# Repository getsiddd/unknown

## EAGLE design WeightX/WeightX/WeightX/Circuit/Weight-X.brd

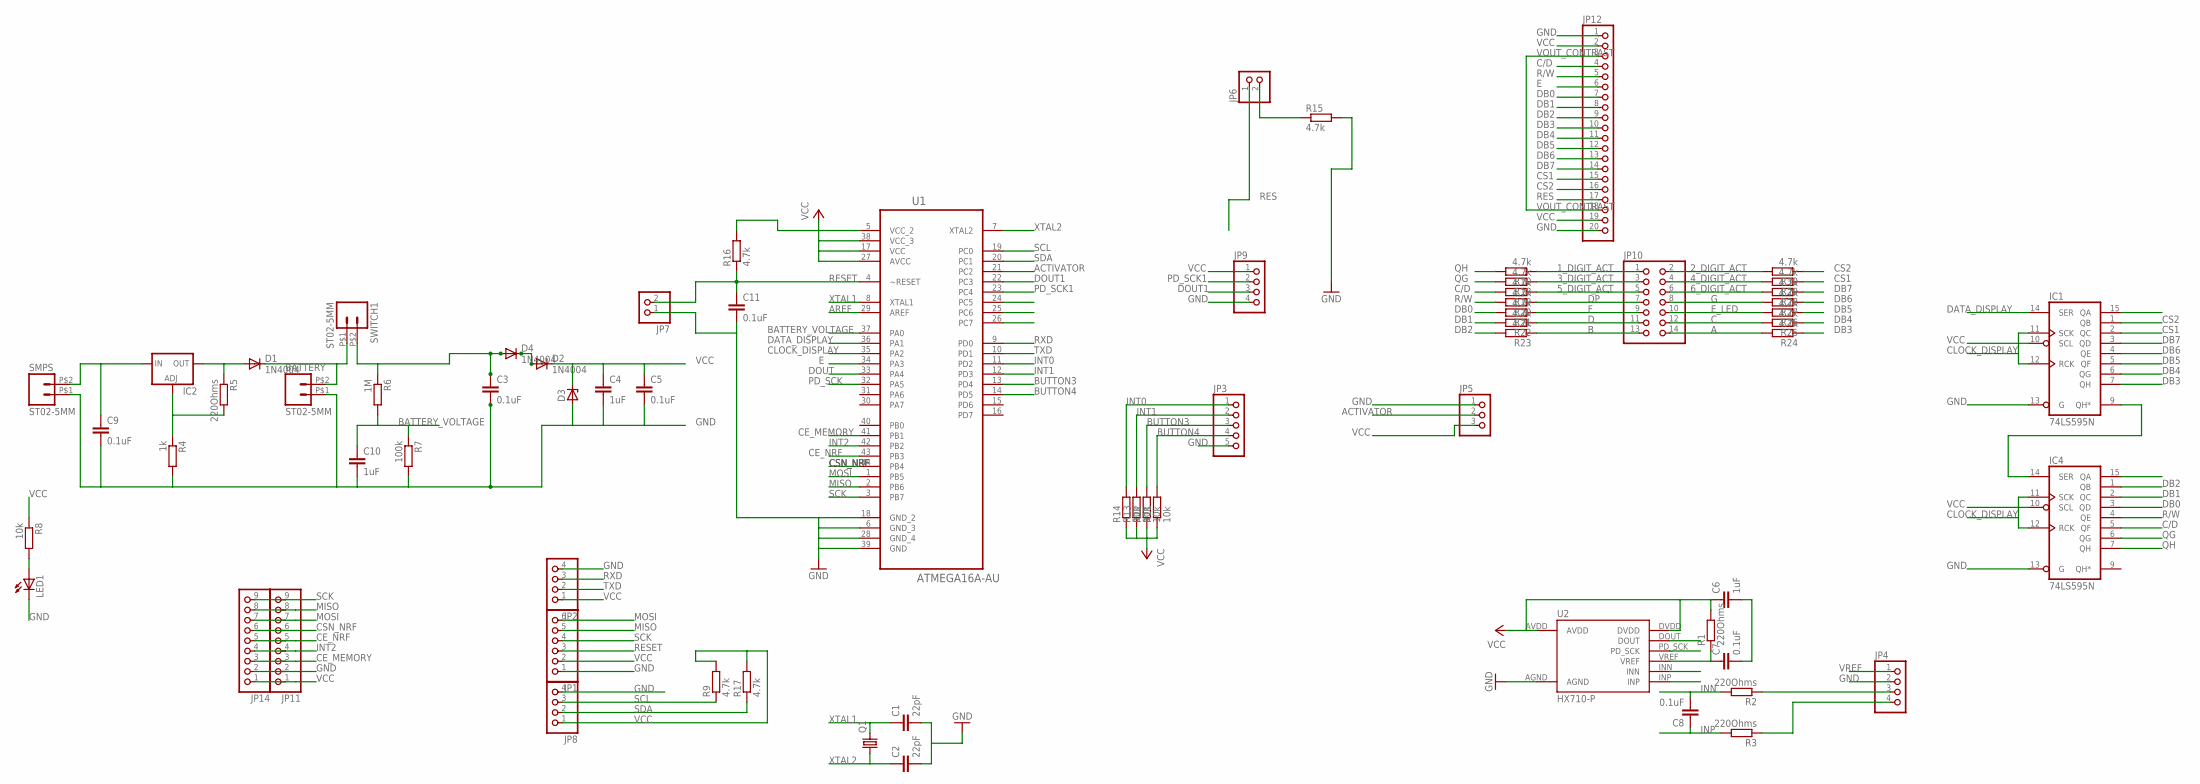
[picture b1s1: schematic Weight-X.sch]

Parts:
BATTERY: ST02-5MM; EK500V-02P
C1, C2: 22pF; C2.5-2
C3, C5, C7, C8, C9, C11: 0.1uF; C5B2.5
C4, C6, C10: 1uF; C5B2.5
D1, D2, D4: 1N4004; DO41-10
D3: ZENER-DIODEC1702-15; C1702-15
IC1, IC4: 74LS595N; DIL16
IC2: LM317TS; 317TS
JP1: PINHD-1X6; 1X06
JP2, JP4, JP8, JP9: PINHD-1X4; 1X04
JP3: PINHD-1X5; 1X05
JP5: PINHD-1X3; 1X03
JP6, JP7: PINHD-1X2; 1X02
JP10: PINHD-2X7; 2X07
JP11, JP14: PINHD-1X9; 1X09
JP12: PINHD-1X20; 1X20
LED1: LED5MM
Q1: CRYSTALHC49U-V; HC49U-V
R1, R2, R3, R5: 220Ohms; 0204/7
R4: 1k; 0204/7
R6: 1M; 0204/7
R7: 100k; 0204/7
R8, R11, R12, R13, R14: 10k; 0204/7
R9, R10, R15, R16, R17, R18, R19, R20, R21, R22, R23, R24, R25, R26, R27, R28, R29, R30: 4.7k; 0204/7
SMPS: ST02-5MM; EK500V-02P
SWITCH1: ST02-5MM; EK500V-02P
U1: ATMEGA16A-AU; QFP80P1200X1200X120-44N
U2: HX710-P; PDIP08_300MIL

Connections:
1_DIGIT_ACT: JP10.1, R10.1
2_DIGIT_ACT: JP10.2, R30.2
3_DIGIT_ACT: JP10.3, R18.1
4_DIGIT_ACT: JP10.4, R29.2
5_DIGIT_ACT: JP10.5, R19.1
6_DIGIT_ACT: JP10.6, R28.2
A: JP10.14, R24.2
ACTIVATOR: JP5.2, U1.21 (PC2)
AREF: U1.29 (AREF)
B: JP10.13, R23.1
BATTERY_VOLTAGE: C10.1, R6.2, R7.1, U1.37 (PA0)
BUTTON3: JP3.3, R12.2, U1.13 (PD4)
BUTTON4: JP3.4, R11.2, U1.14 (PD5)
C: JP10.12, R25.2
C/D: IC4.5 (QF), JP12.4, R19.2
CE_MEMORY: JP11.3, JP14.3, U1.41 (PB1)
CE_NRF: JP11.5, JP14.5, U1.43 (PB3)
CLOCK_DISPLAY: IC1.11 (SCK), IC1.12 (RCK), IC4.11 (SCK), IC4.12 (RCK), U1.35 (PA2)
CS1: IC1.2 (QC), JP12.15, R29.1
CS2: IC1.1 (QB), JP12.16, R30.1
CSN_NRF: JP11.6, JP14.6, U1.44 (PB4)
D: JP10.11, R22.1
DATA_DISPLAY: IC1.14 (SER), U1.36 (PA1)
DB0: IC4.3 (QD), JP12.7, R21.2
DB1: IC4.2 (QC), JP12.8, R22.2
DB2: IC4.1 (QB), JP12.9, R23.2
DB3: IC1.7 (QH), JP12.10, R24.1
DB4: IC1.6 (QG), JP12.11, R25.1
DB5: IC1.5 (QF), JP12.12, R26.1
DB6: IC1.4 (QE), JP12.13, R27.1
DB7: IC1.3 (QD), JP12.14, R28.1
DOUT: U1.33 (PA4), U2.DOUT
DOUT1: JP9.3, U1.22 (PC3)
DP: JP10.7, R20.1
E: JP12.6, U1.34 (PA3)
E_LED: JP10.10, R26.2
F: JP10.9, R21.1
G: JP10.8, R27.2
GND: BATTERY.P$1 (1), C1.2, C2.2, C3.2, C4.2, C5.2, C6.2, C7.2, C9.2, C10.2, C11.2, D3.A, IC1.8 (GND), IC1.13 (G), IC4.8 (GND), IC4.13 (G), JP1.1, JP2.4, JP3.5, JP4.2, JP5.1, JP7.1, JP8.4, JP9.4, JP11.2, JP12.1, JP12.20, JP14.2, LED1.K (C), R4.2, R7.2, R15.2, SMPS.P$1 (1), U1.6 (GND_3), U1.18 (GND_2), U1.28 (GND_4), U1.39 (GND), U2.AGND
INN: C8.2, R2.2, U2.INN
INP: C8.1, R3.2, U2.INP
INT0: JP3.1, R14.2, U1.11 (PD2)
INT1: JP3.2, R13.2, U1.12 (PD3)
INT2: JP11.4, JP14.4, U1.42 (PB2)
MISO: JP1.5, JP11.8, JP14.8, U1.2 (PB6)
MOSI: JP1.6, JP11.7, JP14.7, U1.1 (PB5)
unnamed: BATTERY.P$2 (2), D1.C, SWITCH1.P$1 (1)
unnamed: IC2.1 (ADJ), R4.1, R5.2
unnamed: LED1.A, R8.2
unnamed: D1.A, IC2.2 (OUT), R5.1
unnamed: JP4.3, R2.1
unnamed: D2.A, D4.C
unnamed: C9.1, IC2.3 (IN), SMPS.P$2 (2)
unnamed: C3.1, D4.A, R6.1, SWITCH1.P$2 (2)
unnamed: JP4.4, R3.1
unnamed: JP6.2, R15.1
unnamed: IC1.9 (QH*), IC4.14 (SER)
PD_SCK: U1.32 (PA5), U2.PD_SCK
PD_SCK1: JP9.2, U1.23 (PC4)
QG: IC4.6 (QG), R18.2
QH: IC4.7 (QH), R10.2
R/W: IC4.4 (QE), JP12.5, R20.2
RES: JP6.1, JP12.17
RESET: C11.1, JP1.3, JP7.2, R16.1, U1.4 (~RESET)
RXD: JP2.3, U1.9 (PD0)
SCK: JP1.4, JP11.9, JP14.9, U1.3 (PB7)
SCL: JP8.3, R9.1, U1.19 (PC0)
SDA: JP8.2, R17.1, U1.20 (PC1)
TXD: JP2.2, U1.10 (PD1)
VCC: C4.1, C5.1, C6.1, D2.C, D3.C, IC1.10 (SCL), IC1.16 (VCC), IC4.10 (SCL), IC4.16 (VCC), JP1.2, JP2.1, JP5.3, JP8.1, JP9.1, JP11.1, JP12.2, JP12.19, JP14.1, R1.2, R8.1, R9.2, R11.1, R12.1, R13.1, R14.1, R16.2, R17.2, U1.5 (VCC_2), U1.17 (VCC), U1.27 (AVCC), U1.38 (VCC_3), U2.AVDD, U2.DVDD
VOUT_CONTRAST: JP12.3, JP12.18
VREF: C7.1, JP4.1, R1.1, U2.VREF
XTAL1: C1.1, Q1.2, U1.8 (XTAL1)
XTAL2: C2.1, Q1.1, U1.7 (XTAL2)

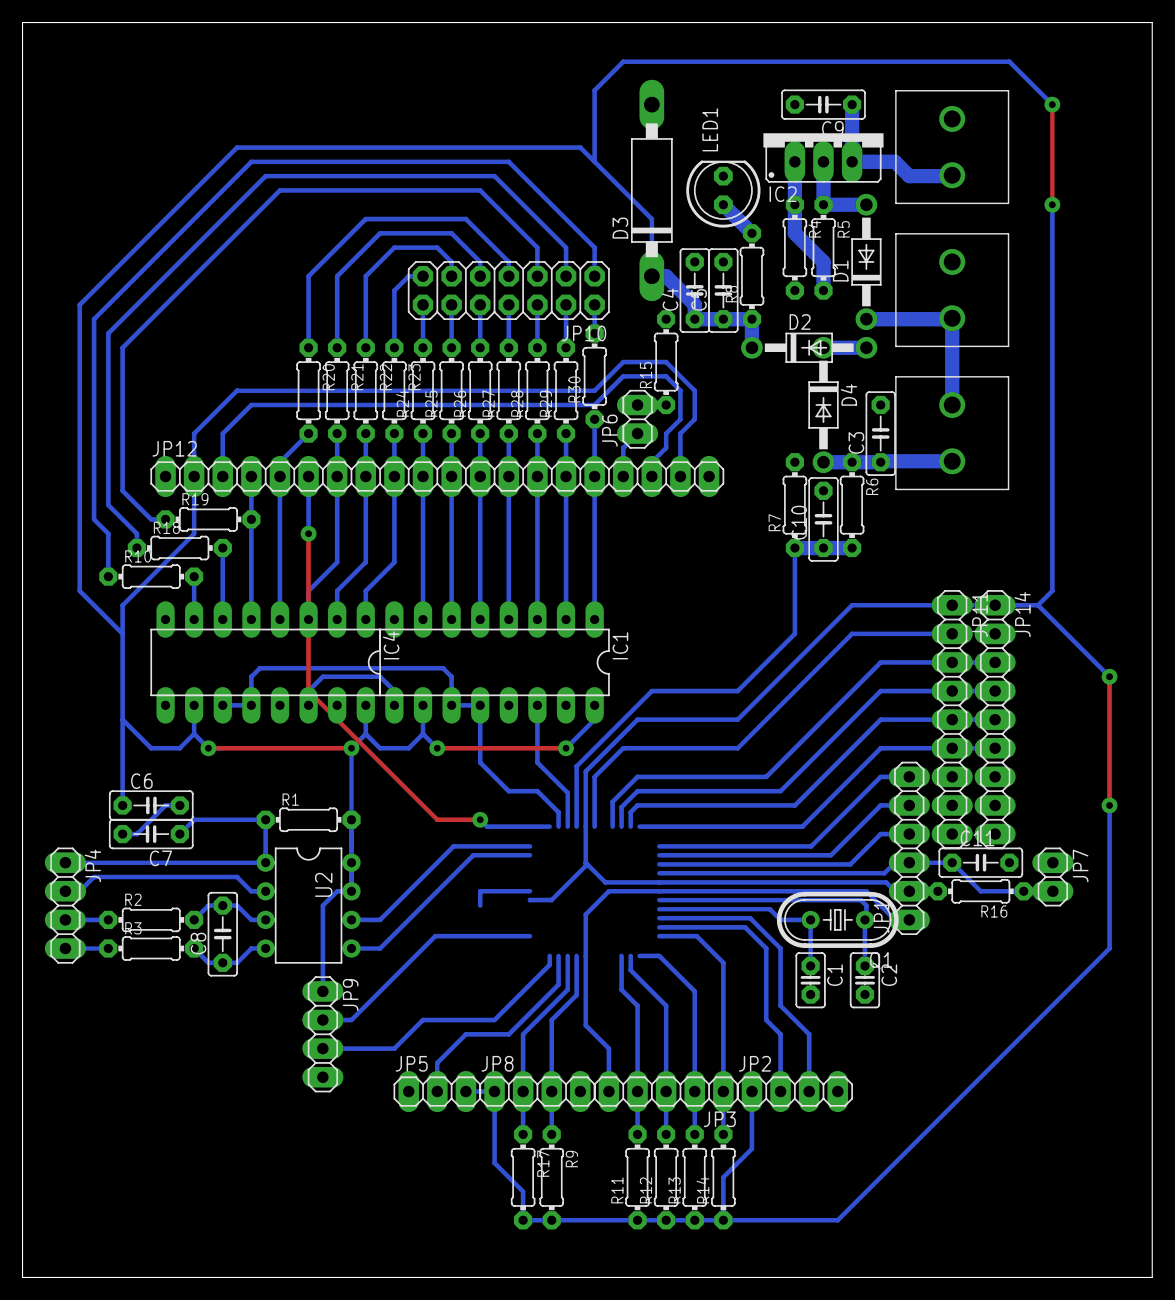
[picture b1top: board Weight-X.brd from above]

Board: 2 copper layers, 100.3 x 111.4 mm, 68 parts (1 on the bottom side), 73 nets.

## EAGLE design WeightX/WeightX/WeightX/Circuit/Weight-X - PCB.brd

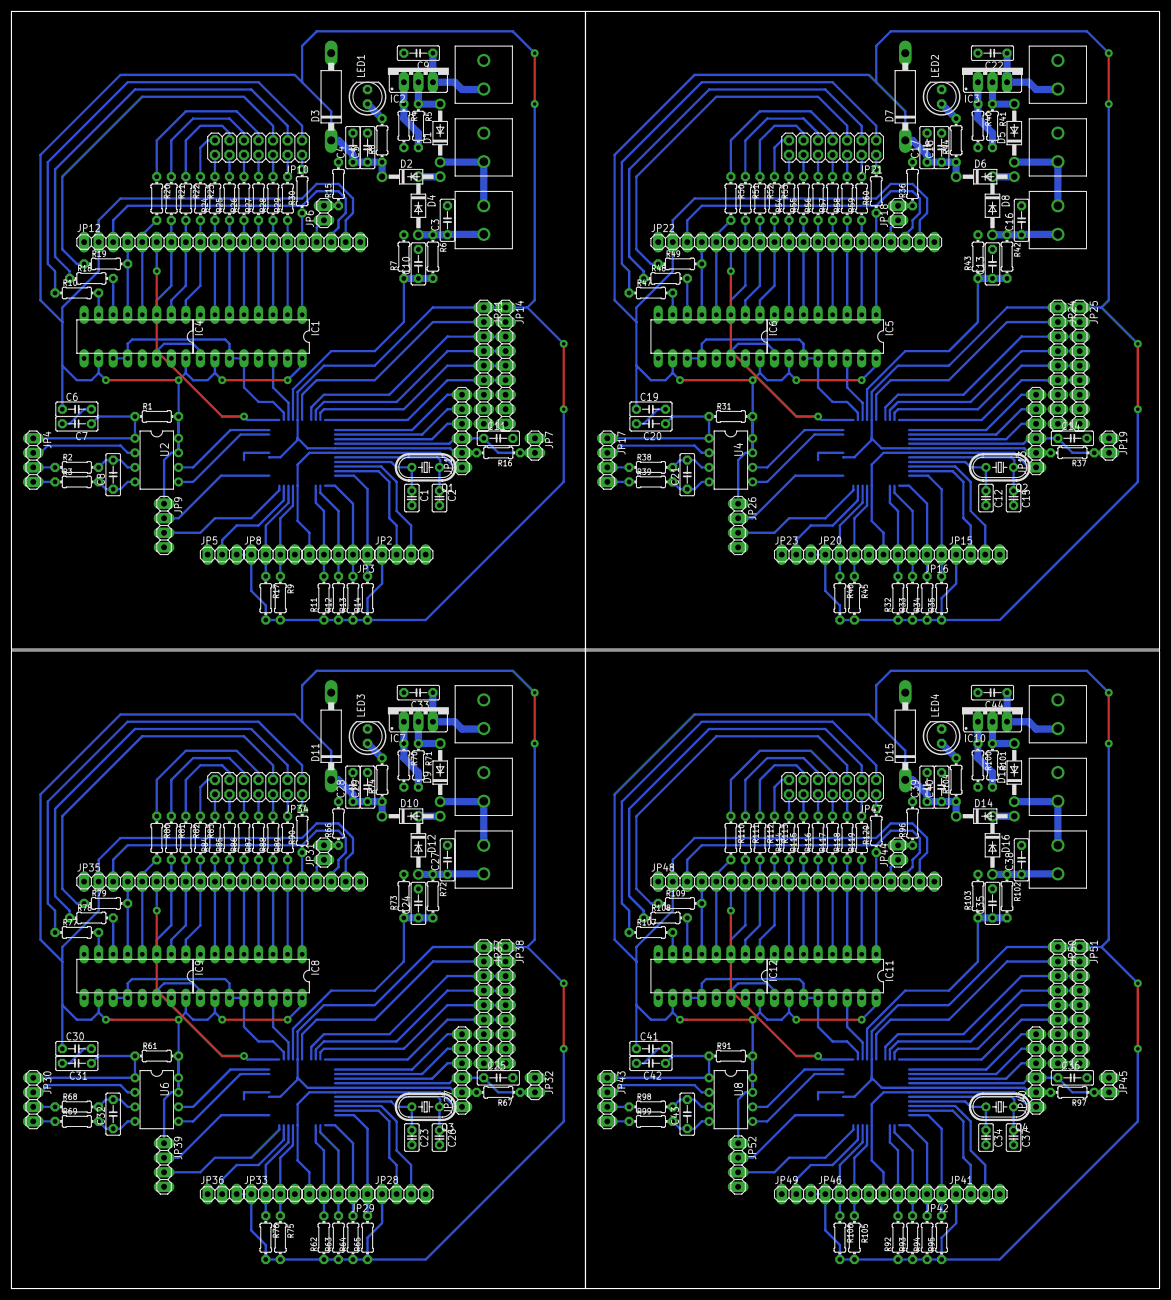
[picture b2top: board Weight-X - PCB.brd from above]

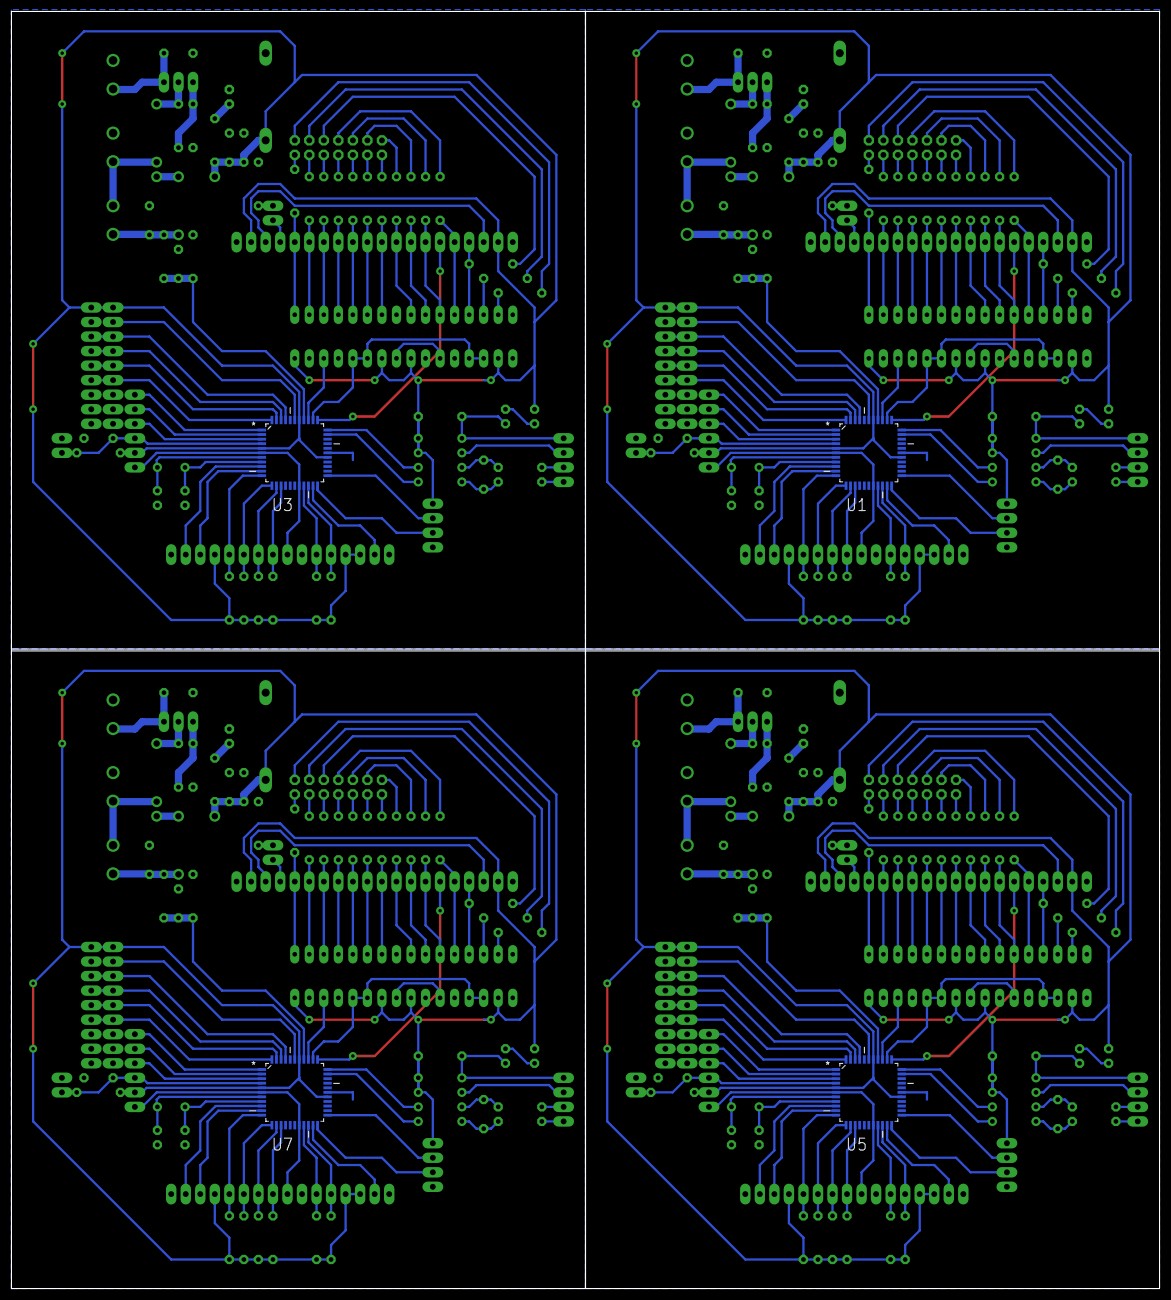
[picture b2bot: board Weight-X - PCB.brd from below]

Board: 2 copper layers, 200.6 x 223.2 mm, 272 parts (4 on the bottom side), 296 nets.

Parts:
BATTERY, BATTERY1, BATTERY2, BATTERY3: ST02-5MM; EK500V-02P
C1, C2, C12, C15, C23, C26, C34, C37: 22pF; C2.5-2
C3, C5, C7, C8, C9, C11, C14, C16, C18, C20, C21, C22, C25, C27, C29, C31, C32, C33, C36, C38, C40, C42, C43, C44: 0.1uF; C5B2.5
C4, C6, C10, C13, C17, C19, C24, C28, C30, C35, C39, C41: 1uF; C5B2.5
D1, D2, D4, D5, D6, D8, D9, D10, D12, D13, D14, D16: 1N4004; DO41-10
D3, D7, D11, D15: C1702-15
IC1, IC4, IC5, IC6, IC8, IC9, IC11, IC12: 74LS595N; DIL16
IC2, IC3, IC7, IC10: 317TS
JP1, JP13, JP27, JP40: 1X06
JP2, JP4, JP8, JP9, JP15, JP17, JP20, JP26, JP28, JP30, JP33, JP39, JP41, JP43, JP46, JP52: 1X04
JP3, JP16, JP29, JP42: 1X05
JP5, JP23, JP36, JP49: 1X03
JP6, JP7, JP18, JP19, JP31, JP32, JP44, JP45: 1X02
JP10, JP21, JP34, JP47: 2X07
JP11, JP14, JP24, JP25, JP37, JP38, JP50, JP51: 1X09
JP12, JP22, JP35, JP48: 1X20
LED1, LED2, LED3, LED4: LED5MM
Q1, Q2, Q3, Q4: HC49U-V
R1, R2, R3, R5, R31, R38, R39, R41, R61, R68, R69, R71, R91, R98, R99, R101: 220Ohms; 0204/7
R4, R40, R70, R100: 1k; 0204/7
R6, R42, R72, R102: 1M; 0204/7
R7, R43, R73, R103: 100k; 0204/7
R8, R11, R12, R13, R14, R32, R33, R34, R35, R44, R62, R63, R64, R65, R74, R92, R93, R94, R95, R104: 10k; 0204/7
R9, R10, R15, R16, R17, R18, R19, R20, R21, R22, R23, R24, R25, R26, R27, R28, R29, R30, R36, R37, R45, R46, R47, R48, R49, R50, R51, R52, R53, R54, R55, R56, R57, R58, R59, R60, R66, R67, R75, R76, R77, R78, R79, R80, R81, R82, R83, R84, R85, R86, R87, R88, R89, R90, R96, R97, R105, R106, R107, R108, R109, R110, R111, R112, R113, R114, R115, R116, R117, R118, R119, R120: 4.7k; 0204/7
SMPS, SMPS1, SMPS2, SMPS3: ST02-5MM; EK500V-02P
SWITCH1, SWITCH2, SWITCH3, SWITCH4: ST02-5MM; EK500V-02P
U1, U3, U5, U7: ATMEGA16A-AU; QFP80P1200X1200X120-44N
U2, U4, U6, U8: HX710-P; PDIP08_300MIL

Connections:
1_DIGIT_ACT: JP10.1, R10.1
1_DIGIT_ACT1: JP21.1, R47.1
1_DIGIT_ACT2: JP34.1, R77.1
1_DIGIT_ACT3: JP47.1, R107.1
2_DIGIT_ACT: JP10.2, R30.2
2_DIGIT_ACT1: JP21.2, R60.2
2_DIGIT_ACT2: JP34.2, R90.2
2_DIGIT_ACT3: JP47.2, R120.2
3_DIGIT_ACT: JP10.3, R18.1
3_DIGIT_ACT1: JP21.3, R48.1
3_DIGIT_ACT2: JP34.3, R78.1
3_DIGIT_ACT3: JP47.3, R108.1
4_DIGIT_ACT: JP10.4, R29.2
4_DIGIT_ACT1: JP21.4, R59.2
4_DIGIT_ACT2: JP34.4, R89.2
4_DIGIT_ACT3: JP47.4, R119.2
5_DIGIT_ACT: JP10.5, R19.1
5_DIGIT_ACT1: JP21.5, R49.1
5_DIGIT_ACT2: JP34.5, R79.1
5_DIGIT_ACT3: JP47.5, R109.1
6_DIGIT_ACT: JP10.6, R28.2
6_DIGIT_ACT1: JP21.6, R58.2
6_DIGIT_ACT2: JP34.6, R88.2
6_DIGIT_ACT3: JP47.6, R118.2
A: JP10.14, R24.2
A1: JP21.14, R54.2
A2: JP34.14, R84.2
A3: JP47.14, R114.2
ACTIVATOR: JP5.2, U1.21
ACTIVATOR1: JP23.2, U3.21
ACTIVATOR2: JP36.2, U5.21
ACTIVATOR3: JP49.2, U7.21
B: JP10.13, R23.1
B1: JP21.13, R53.1
B2: JP34.13, R83.1
B3: JP47.13, R113.1
BATTERY_VOLTAGE: C10.1, R6.2, R7.1, U1.37
BATTERY_VOLTAGE1: C13.1, R42.2, R43.1, U3.37
BATTERY_VOLTAGE2: C24.1, R72.2, R73.1, U5.37
BATTERY_VOLTAGE3: C35.1, R102.2, R103.1, U7.37
BUTTON1: JP16.3, R33.2, U3.13
BUTTON2: JP16.4, R32.2, U3.14
BUTTON3: JP3.3, R12.2, U1.13
BUTTON4: JP3.4, R11.2, U1.14
BUTTON5: JP29.3, R63.2, U5.13
BUTTON6: JP29.4, R62.2, U5.14
BUTTON7: JP42.3, R93.2, U7.13
BUTTON8: JP42.4, R92.2, U7.14
C: JP10.12, R25.2
C1: JP21.12, R55.2
C2: JP34.12, R85.2
C3: JP47.12, R115.2
C/D: IC4.5, JP12.4, R19.2
C/D1: IC6.5, JP22.4, R49.2
C/D2: IC9.5, JP35.4, R79.2
C/D3: IC12.5, JP48.4, R109.2
CE_MEMORY: JP11.3, JP14.3, U1.41
CE_MEMORY1: JP24.3, JP25.3, U3.41
CE_MEMORY2: JP37.3, JP38.3, U5.41
CE_MEMORY3: JP50.3, JP51.3, U7.41
CE_NRF: JP11.5, JP14.5, U1.43
CE_NRF1: JP24.5, JP25.5, U3.43
CE_NRF2: JP37.5, JP38.5, U5.43
CE_NRF3: JP50.5, JP51.5, U7.43
CLOCK_DISPLAY: IC1.11, IC1.12, IC4.11, IC4.12, U1.35
CLOCK_DISPLAY1: IC5.11, IC5.12, IC6.11, IC6.12, U3.35
CLOCK_DISPLAY2: IC8.11, IC8.12, IC9.11, IC9.12, U5.35
CLOCK_DISPLAY3: IC11.11, IC11.12, IC12.11, IC12.12, U7.35
CS1: IC1.2, JP12.15, R29.1
CS2: IC1.1, JP12.16, R30.1
CS3: IC5.2, JP22.15, R59.1
CS4: IC5.1, JP22.16, R60.1
CS5: IC8.2, JP35.15, R89.1
CS6: IC8.1, JP35.16, R90.1
CS7: IC11.2, JP48.15, R119.1
CS8: IC11.1, JP48.16, R120.1
CSN_NRF: JP11.6, JP14.6, U1.44
CSN_NRF1: JP24.6, JP25.6, U3.44
CSN_NRF2: JP37.6, JP38.6, U5.44
CSN_NRF3: JP50.6, JP51.6, U7.44
D: JP10.11, R22.1
D1: JP21.11, R52.1
D2: JP34.11, R82.1
D3: JP47.11, R112.1
DATA_DISPLAY: IC1.14, U1.36
DATA_DISPLAY1: IC5.14, U3.36
DATA_DISPLAY2: IC8.14, U5.36
DATA_DISPLAY3: IC11.14, U7.36
DB0: IC4.3, JP12.7, R21.2
DB1: IC4.2, JP12.8, R22.2
DB2: IC4.1, JP12.9, R23.2
DB3: IC1.7, JP12.10, R24.1
DB4: IC1.6, JP12.11, R25.1
DB5: IC1.5, JP12.12, R26.1
DB6: IC1.4, JP12.13, R27.1
DB7: IC1.3, JP12.14, R28.1
DB8: IC6.3, JP22.7, R51.2
DB9: IC6.2, JP22.8, R52.2
DB10: IC6.1, JP22.9, R53.2
DB11: IC5.7, JP22.10, R54.1
DB12: IC5.6, JP22.11, R55.1
DB13: IC5.5, JP22.12, R56.1
DB14: IC5.4, JP22.13, R57.1
DB15: IC5.3, JP22.14, R58.1
DB16: IC9.3, JP35.7, R81.2
DB17: IC9.2, JP35.8, R82.2
DB18: IC9.1, JP35.9, R83.2
DB19: IC8.7, JP35.10, R84.1
DB20: IC8.6, JP35.11, R85.1
DB21: IC8.5, JP35.12, R86.1
DB22: IC8.4, JP35.13, R87.1
DB23: IC8.3, JP35.14, R88.1
DB24: IC12.3, JP48.7, R111.2
DB25: IC12.2, JP48.8, R112.2
DB26: IC12.1, JP48.9, R113.2
DB27: IC11.7, JP48.10, R114.1
DB28: IC11.6, JP48.11, R115.1
DB29: IC11.5, JP48.12, R116.1
DB30: IC11.4, JP48.13, R117.1
DB31: IC11.3, JP48.14, R118.1
DOUT: U1.33, U2.DOUT
DOUT1: JP9.3, U1.22
DOUT2: U3.33, U4.DOUT
DOUT3: JP26.3, U3.22
DOUT4: U5.33, U6.DOUT
DOUT5: JP39.3, U5.22
DOUT6: U7.33, U8.DOUT
DOUT7: JP52.3, U7.22
DP: JP10.7, R20.1
DP1: JP21.7, R50.1
DP2: JP34.7, R80.1
DP3: JP47.7, R110.1
E: JP12.6, U1.34
E1: JP22.6, U3.34
E2: JP35.6, U5.34
E3: JP48.6, U7.34
E_LED: JP10.10, R26.2
E_LED1: JP21.10, R56.2
E_LED2: JP34.10, R86.2
E_LED3: JP47.10, R116.2
F: JP10.9, R21.1
F1: JP21.9, R51.1
F2: JP34.9, R81.1
F3: JP47.9, R111.1
G: JP10.8, R27.2
G1: JP21.8, R57.2
G2: JP34.8, R87.2
G3: JP47.8, R117.2
GND: BATTERY.P$1, C1.2, C2.2, C3.2, C4.2, C5.2, C9.2, C10.2, C11.2, D3.A, IC1.8, IC1.13, IC4.8, IC4.13, JP1.1, JP2.4, JP3.5, JP4.2, JP5.1, JP7.1, JP8.4, JP9.4, JP11.2, JP12.1, JP12.20, JP14.2, LED1.K, R4.2, R7.2, R15.2, SMPS.P$1, U1.6, U1.18, U1.28, U1.39, U2.AGND
GND1: BATTERY1.P$1, C12.2, C13.2, C14.2, C15.2, C16.2, C17.2, C18.2, C22.2, D7.A, IC5.8, IC5.13, IC6.8, IC6.13, JP13.1, JP15.4, JP16.5, JP17.2, JP19.1, JP20.4, JP22.1, JP22.20, JP23.1, JP24.2, JP25.2, JP26.4, LED2.K, R36.2, R40.2, R43.2, SMPS1.P$1, U3.6, U3.18, U3.28, U3.39, U4.AGND
GND2: BATTERY2.P$1, C23.2, C24.2, C25.2, C26.2, C27.2, C28.2, C29.2, C33.2, D11.A, IC8.8, IC8.13, IC9.8, IC9.13, JP27.1, JP28.4, JP29.5, JP30.2, JP32.1, JP33.4, JP35.1, JP35.20, JP36.1, JP37.2, JP38.2, JP39.4, LED3.K, R66.2, R70.2, R73.2, SMPS2.P$1, U5.6, U5.18, U5.28, U5.39, U6.AGND
GND3: BATTERY3.P$1, C34.2, C35.2, C36.2, C37.2, C38.2, C39.2, C40.2, C44.2, D15.A, IC11.8, IC11.13, IC12.8, IC12.13, JP40.1, JP41.4, JP42.5, JP43.2, JP45.1, JP46.4, JP48.1, JP48.20, JP49.1, JP50.2, JP51.2, JP52.4, LED4.K, R96.2, R100.2, R103.2, SMPS3.P$1, U7.6, U7.18, U7.28, U7.39, U8.AGND
INN: C8.2, R2.2, U2.INN
INN1: C21.2, R38.2, U4.INN
INN2: C32.2, R68.2, U6.INN
INN3: C43.2, R98.2, U8.INN
INP: C8.1, R3.2, U2.INP
INP1: C21.1, R39.2, U4.INP
INP2: C32.1, R69.2, U6.INP
INP3: C43.1, R99.2, U8.INP
INT0: JP3.1, R14.2, U1.11
INT1: JP3.2, R13.2, U1.12
INT2: JP11.4, JP14.4, U1.42
INT3: JP16.1, R35.2, U3.11
INT4: JP16.2, R34.2, U3.12
INT5: JP24.4, JP25.4, U3.42
INT6: JP29.1, R65.2, U5.11
INT7: JP29.2, R64.2, U5.12
INT8: JP37.4, JP38.4, U5.42
INT9: JP42.1, R95.2, U7.11
INT10: JP42.2, R94.2, U7.12
INT11: JP50.4, JP51.4, U7.42
MISO: JP1.5, JP11.8, JP14.8, U1.2
MISO1: JP13.5, JP24.8, JP25.8, U3.2
MISO2: JP27.5, JP37.8, JP38.8, U5.2
MISO3: JP40.5, JP50.8, JP51.8, U7.2
MOSI: JP1.6, JP11.7, JP14.7, U1.1
MOSI1: JP13.6, JP24.7, JP25.7, U3.1
MOSI2: JP27.6, JP37.7, JP38.7, U5.1
MOSI3: JP40.6, JP50.7, JP51.7, U7.1
unnamed: BATTERY.P$2, D1.C, SWITCH1.P$1
unnamed: IC2.1, R4.1, R5.2
unnamed: LED1.A, R8.2
unnamed: D1.A, IC2.2, R5.1
unnamed: JP4.3, R2.1
unnamed: D2.A, D4.C
unnamed: C9.1, IC2.3, SMPS.P$2
unnamed: C19.2, C20.2
unnamed: C6.2, C7.2
unnamed: C3.1, D4.A, R6.1, SWITCH1.P$2
unnamed: JP4.4, R3.1
unnamed: JP17.3, R38.1
unnamed: JP6.2, R15.1
unnamed: JP17.4, R39.1
unnamed: IC1.9, IC4.14
unnamed: IC3.1, R40.1, R41.2
unnamed: D5.A, IC3.2, R41.1
unnamed: C22.1, IC3.3, SMPS1.P$2
unnamed: C16.1, D8.A, R42.1, SWITCH2.P$2
unnamed: JP18.2, R36.1
unnamed: BATTERY1.P$2, D5.C, SWITCH2.P$1
unnamed: LED2.A, R44.2
unnamed: D6.A, D8.C
unnamed: IC5.9, IC6.14
unnamed: C30.2, C31.2
unnamed: JP30.3, R68.1
unnamed: JP30.4, R69.1
unnamed: IC7.1, R70.1, R71.2
unnamed: D9.A, IC7.2, R71.1
unnamed: C33.1, IC7.3, SMPS2.P$2
unnamed: C27.1, D12.A, R72.1, SWITCH3.P$2
unnamed: JP31.2, R66.1
unnamed: BATTERY2.P$2, D9.C, SWITCH3.P$1
unnamed: LED3.A, R74.2
unnamed: D10.A, D12.C
unnamed: IC8.9, IC9.14
unnamed: C41.2, C42.2
unnamed: JP43.3, R98.1
unnamed: JP43.4, R99.1
unnamed: IC10.1, R100.1, R101.2
unnamed: D13.A, IC10.2, R101.1
unnamed: C44.1, IC10.3, SMPS3.P$2
unnamed: C38.1, D16.A, R102.1, SWITCH4.P$2
unnamed: JP44.2, R96.1
unnamed: BATTERY3.P$2, D13.C, SWITCH4.P$1
unnamed: LED4.A, R104.2
unnamed: D14.A, D16.C
unnamed: IC11.9, IC12.14
PD_SCK: U1.32, U2.PD_SCK
PD_SCK1: JP9.2, U1.23
PD_SCK2: U3.32, U4.PD_SCK
PD_SCK3: JP26.2, U3.23
PD_SCK4: U5.32, U6.PD_SCK
PD_SCK5: JP39.2, U5.23
PD_SCK6: U7.32, U8.PD_SCK
PD_SCK7: JP52.2, U7.23
QG: IC4.6, R18.2
QG1: IC6.6, R48.2
QG2: IC9.6, R78.2
QG3: IC12.6, R108.2
QH: IC4.7, R10.2
QH1: IC6.7, R47.2
QH2: IC9.7, R77.2
QH3: IC12.7, R107.2
R/W: IC4.4, JP12.5, R20.2
R/W1: IC6.4, JP22.5, R50.2
R/W2: IC9.4, JP35.5, R80.2
R/W3: IC12.4, JP48.5, R110.2
RES: JP6.1, JP12.17
RES1: JP18.1, JP22.17
RES2: JP31.1, JP35.17
RES3: JP44.1, JP48.17
RESET: C11.1, JP1.3, JP7.2, R16.1, U1.4
RESET1: C14.1, JP13.3, JP19.2, R37.1, U3.4
RESET2: C25.1, JP27.3, JP32.2, R67.1, U5.4
RESET3: C36.1, JP40.3, JP45.2, R97.1, U7.4
RXD: JP2.3, U1.9
RXD1: JP15.3, U3.9
RXD2: JP28.3, U5.9
RXD3: JP41.3, U7.9
SCK: JP1.4, JP11.9, JP14.9, U1.3
SCK1: JP13.4, JP24.9, JP25.9, U3.3
SCK2: JP27.4, JP37.9, JP38.9, U5.3
SCK3: JP40.4, JP50.9, JP51.9, U7.3
SCL: JP8.3, R9.1, U1.19
SCL1: JP20.3, R45.1, U3.19
SCL2: JP33.3, R75.1, U5.19
SCL3: JP46.3, R105.1, U7.19
SDA: JP8.2, R17.1, U1.20
SDA1: JP20.2, R46.1, U3.20
SDA2: JP33.2, R76.1, U5.20
SDA3: JP46.2, R106.1, U7.20
TXD: JP2.2, U1.10
TXD1: JP15.2, U3.10
TXD2: JP28.2, U5.10
TXD3: JP41.2, U7.10
VCC: C4.1, C5.1, C6.1, D2.C, D3.C, IC1.10, IC1.16, IC4.10, IC4.16, JP1.2, JP2.1, JP5.3, JP8.1, JP9.1, JP11.1, JP12.2, JP12.19, JP14.1, R1.2, R8.1, R9.2, R11.1, R12.1, R13.1, R14.1, R16.2, R17.2, U1.5, U1.17, U1.27, U1.38, U2.AVDD, U2.DVDD
VCC1: C17.1, C18.1, C19.1, D6.C, D7.C, IC5.10, IC5.16, IC6.10, IC6.16, JP13.2, JP15.1, JP20.1, JP22.2, JP22.19, JP23.3, JP24.1, JP25.1, JP26.1, R31.2, R32.1, R33.1, R34.1, R35.1, R37.2, R44.1, R45.2, R46.2, U3.5, U3.17, U3.27, U3.38, U4.AVDD, U4.DVDD
VCC2: C28.1, C29.1, C30.1, D10.C, D11.C, IC8.10, IC8.16, IC9.10, IC9.16, JP27.2, JP28.1, JP33.1, JP35.2, JP35.19, JP36.3, JP37.1, JP38.1, JP39.1, R61.2, R62.1, R63.1, R64.1, R65.1, R67.2, R74.1, R75.2, R76.2, U5.5, U5.17, U5.27, U5.38, U6.AVDD, U6.DVDD
VCC3: C39.1, C40.1, C41.1, D14.C, D15.C, IC11.10, IC11.16, IC12.10, IC12.16, JP40.2, JP41.1, JP46.1, JP48.2, JP48.19, JP49.3, JP50.1, JP51.1, JP52.1, R91.2, R92.1, R93.1, R94.1, R95.1, R97.2, R104.1, R105.2, R106.2, U7.5, U7.17, U7.27, U7.38, U8.AVDD, U8.DVDD
VOUT_CONTRAST: JP12.3, JP12.18
VOUT_CONTRAST1: JP22.3, JP22.18
VOUT_CONTRAST2: JP35.3, JP35.18
VOUT_CONTRAST3: JP48.3, JP48.18
VREF: C7.1, JP4.1, R1.1, U2.VREF
VREF1: C20.1, JP17.1, R31.1, U4.VREF
VREF2: C31.1, JP30.1, R61.1, U6.VREF
VREF3: C42.1, JP43.1, R91.1, U8.VREF
XTAL1: C1.1, Q1.2, U1.8
XTAL2: C2.1, Q1.1, U1.7
XTAL3: C12.1, Q2.2, U3.8
XTAL4: C15.1, Q2.1, U3.7
XTAL5: C23.1, Q3.2, U5.8
XTAL6: C26.1, Q3.1, U5.7
XTAL7: C34.1, Q4.2, U7.8
XTAL8: C37.1, Q4.1, U7.7

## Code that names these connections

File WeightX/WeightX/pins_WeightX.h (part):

#define PD_SCK_PORT         PORTA                           // Power Down and Serial Clock Input Port
#define PD_SCK_DDR          DDRA                            // Power Down and Serial Clock DDR
#define PD_SCK_PIN          PA5                             // Power Down and Serial Clock Pin
#define PD_SCK_SET_OUTPUT   PD_SCK_DDR |= (1<<PD_SCK_PIN)
#define PD_SCK_SET_HIGH     PD_SCK_PORT |= (1<<PD_SCK_PIN)
#define PD_SCK_SET_LOW      PD_SCK_PORT &= ~(1<<PD_SCK_PIN)

#define DOUT_PORT           PORTA                           // Serial Data Output Port
#define DOUT_DDR            DDRA                            // Serial Data Output DDR
#define DOUT_INPUT          PINA                            // Serial Data Output Input
#define DOUT_PIN            PA4                             // Serial Data Output Pin
#define DOUT_READ           (DOUT_INPUT & (1<<DOUT_PIN))    // Serial Data Output Read Pin
#define DOUT_SET_HIGH       DOUT_PORT |= (1<<DOUT_PIN)  
#define DOUT_SET_LOW        DOUT_PORT &= ~(1<<DOUT_PIN) 
#define DOUT_SET_INPUT      DOUT_DDR &= ~(1<<DOUT_PIN); DOUT_SET_HIGH
#define DOUT_SET_OUTPUT     DOUT_DDR |= (1<<DOUT_PIN);  DOUT_SET_LOW

#define BATTERY_PORT           PORTA                           
#define BATTERY_DDR            DDRA                            
#define BATTERY_INPUT          PINA                            
#define BATTERY_PIN            PA0                             
#define BATTERY_READ           (BATTERY_INPUT & (1<<BATTERY_PIN))    
#define BATTERY_SET_HIGH       BATTERY_PORT |= (1<<BATTERY_PIN)
#define BATTERY_SET_LOW        BATTERY_PORT &= ~(1<<BATTERY_PIN)
#define BATTERY_SET_INPUT      BATTERY_DDR &= ~(1<<BATTERY_PIN); BATTERY_SET_HIGH
#define BATTERY_SET_OUTPUT     BATTERY_DDR |= (1<<BATTERY_PIN);  BATTERY_SET_LOW

#define DATA_DISPLAY_PORT           PORTA
#define DATA_DISPLAY_DDR            DDRA
#define DATA_DISPLAY_INPUT          PINA
#define DATA_DISPLAY_PIN            PA1
#define DATA_DISPLAY_READ           (DATA_DISPAY_INPUT & (1<<DATA_DISPAY_PIN))
#define DATA_DISPLAY_SET_HIGH       DATA_DISPAY_PORT |= (1<<DATA_DISPAY_PIN)
#define DATA_DISPLAY_SET_LOW        DATA_DISPAY_PORT &= ~(1<<DATA_DISPAY_PIN)
#define DATA_DISPLAY_SET_INPUT      DATA_DISPAY_DDR &= ~(1<<DATA_DISPAY_PIN); DATA_DISPAY_SET_HIGH
#define DATA_DISPLAY_SET_OUTPUT     DATA_DISPAY_DDR |= (1<<DATA_DISPAY_PIN);  DATA_DISPAY_SET_LOW

#define CLOCK_DISPLAY_PORT           PORTA
#define CLOCK_DISPLAY_DDR            DDRA
#define CLOCK_DISPLAY_INPUT          PINA
#define CLOCK_DISPLAY_PIN            PA2
#define CLOCK_DISPLAY_READ           (CLOCK_DISPLAY_INPUT & (1<<CLOCK_DISPLAY_PIN))
#define CLOCK_DISPLAY_SET_HIGH       CLOCK_DISPLAY_PORT |= (1<<CLOCK_DISPLAY_PIN)
#define CLOCK_DISPLAY_SET_LOW        CLOCK_DISPLAY_PORT &= ~(1<<CLOCK_DISPLAY_PIN)
#define CLOCK_DISPLAY_SET_INPUT      CLOCK_DISPLAY_DDR &= ~(1<<CLOCK_DISPLAY_PIN); CLOCK_DISPLAY_SET_HIGH
#define CLOCK_DISPLAY_SET_OUTPUT     CLOCK_DISPLAY_DDR |= (1<<CLOCK_DISPLAY_PIN);  CLOCK_DISPLAY_SET_LOW

#define ENABLE_DISPLAY_PORT           PORTA
#define ENABLE_DISPLAY_DDR            DDRA
#define ENABLE_DISPLAY_INPUT          PINA
#define ENABLE_DISPLAY_PIN            PA2
#define ENABLE_DISPLAY_READ           (ENABLE_DISPLAY_INPUT & (1<<ENABLE_DISPLAY_PIN))
#define ENABLE_DISPLAY_SET_HIGH       ENABLE_DISPLAY_PORT |= (1<<ENABLE_DISPLAY_PIN)
#define ENABLE_DISPLAY_SET_LOW        ENABLE_DISPLAY_PORT &= ~(1<<ENABLE_DISPLAY_PIN)
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#define ACTIVATOR_DISPLAY_PORT           PORTC
#define ACTIVATOR_DISPLAY_DDR            DDRC
#define ACTIVATOR_DISPLAY_INPUT          PINC
#define ACTIVATOR_DISPLAY_PIN            PC2
#define ACTIVATOR_DISPLAY_READ           (ACTIVATOR_DISPLAY_INPUT & (1<<ACTIVATOR_DISPLAY_PIN))
#define ACTIVATOR_DISPLAY_SET_HIGH       ACTIVATOR_DISPLAY_PORT |= (1<<ACTIVATOR_DISPLAY_PIN)
#define ACTIVATOR_DISPLAY_SET_LOW        ACTIVATOR_DISPLAY_PORT &= ~(1<<ACTIVATOR_DISPLAY_PIN)
#define ACTIVATOR_DISPLAY_SET_INPUT      ACTIVATOR_DISPLAY_DDR &= ~(1<<ACTIVATOR_DISPLAY_PIN); ACTIVATOR_DISPLAY_SET_HIGH
#define ACTIVATOR_DISPLAY_SET_OUTPUT     ACTIVATOR_DISPLAY_DDR |= (1<<ACTIVATOR_DISPLAY_PIN);  ACTIVATOR_DISPLAY_SET_LOW

#define PD_SCK1_PORT         PORTC                           // Power Down and Serial Clock Input Port
#define PD_SCK1_DDR          DDRC                            // Power Down and Serial Clock DDR
#define PD_SCK1_PIN          PC4                             // Power Down and Serial Clock Pin
#define PD_SCK1_SET_OUTPUT   PD_SCK_DDR |= (1<<PD_SCK_PIN)
#define PD_SCK1_SET_HIGH     PD_SCK_PORT |= (1<<PD_SCK_PIN)
#define PD_SCK1_SET_LOW      PD_SCK_PORT &= ~(1<<PD_SCK_PIN)

#define DOUT1_PORT           PORTC                           // Serial Data Output Port
#define DOUT1_DDR            DDRC                            // Serial Data Output DDR
#define DOUT1_INPUT          PINC                            // Serial Data Output Input
#define DOUT1_PIN            PC3                             // Serial Data Output Pin
#define DOUT1_READ           (DOUT1_INPUT & (1<<DOUT1_PIN))    // Serial Data Output Read Pin
#define DOUT1_SET_HIGH       DOUT1_PORT |= (1<<DOUT1_PIN)
#define DOUT1_SET_LOW        DOUT1_PORT &= ~(1<<DOUT1_PIN)
#define DOUT1_SET_INPUT      DOUT1_DDR &= ~(1<<DOUT1_PIN); DOUT1_SET_HIGH
#define DOUT1_SET_OUTPUT     DOUT1_DDR |= (1<<DOUT1_PIN);  DOUT1_SET_LOW

#define BUTTON1_PORT           PORTD                           // Serial Data Output Port
#define BUTTON1_DDR            DDRD                            // Serial Data Output DDR
#define BUTTON1_INPUT          PIND                            // Serial Data Output Input
#define BUTTON1_PIN            PD2                             // Serial Data Output Pin
#define BUTTON1_READ           (BUTTON1_INPUT & (1<<BUTTON1_PIN))    // Serial Data Output Read Pin
#define BUTTON1_SET_HIGH       BUTTON1_PORT |= (1<<BUTTON1_PIN)
#define BUTTON1_SET_LOW        BUTTON1_PORT &= ~(1<<BUTTON1_PIN)
#define BUTTON1_SET_INPUT      BUTTON1_DDR &= ~(1<<BUTTON1_PIN); BUTTON1_SET_HIGH
#define BUTTON1_SET_OUTPUT     BUTTON1_DDR |= (1<<BUTTON1_PIN);  BUTTON1_SET_LOW

#define BUTTON2_PORT           PORTD                           // Serial Data Output Port
#define BUTTON2_DDR            DDRD                            // Serial Data Output DDR
#define BUTTON2_INPUT          PIND                            // Serial Data Output Input
#define BUTTON2_PIN            PD3                             // Serial Data Output Pin
#define BUTTON2_READ           (BUTTON2_INPUT & (1<<BUTTON2_PIN))    // Serial Data Output Read Pin
#define BUTTON2_SET_HIGH       BUTTON2_PORT |= (1<<BUTTON2_PIN)
#define BUTTON2_SET_LOW        BUTTON2_PORT &= ~(1<<BUTTON2_PIN)
#define BUTTON2_SET_INPUT      BUTTON2_DDR &= ~(1<<BUTTON2_PIN); BUTTON2_SET_HIGH
#define BUTTON2_SET_OUTPUT     BUTTON2_DDR |= (1<<BUTTON2_PIN);  BUTTON2_SET_LOW

#define BUTTON3_PORT           PORTD                           // Serial Data Output Port
#define BUTTON3_DDR            DDRD                            // Serial Data Output DDR
#define BUTTON3_INPUT          PIND                            // Serial Data Output Input
#define BUTTON3_PIN            PD4                             // Serial Data Output Pin
#define BUTTON3_READ           (BUTTON3_INPUT & (1<<BUTTON3_PIN))    // Serial Data Output Read Pin
#define BUTTON3_SET_HIGH       BUTTON3_PORT |= (1<<BUTTON3_PIN)
#define BUTTON3_SET_LOW        BUTTON3_PORT &= ~(1<<BUTTON3_PIN)
#define BUTTON3_SET_INPUT      BUTTON3_DDR &= ~(1<<BUTTON3_PIN); BUTTON3_SET_HIGH
#define BUTTON3_SET_OUTPUT     BUTTON3_DDR |= (1<<BUTTON3_PIN);  BUTTON3_SET_LOW

#define BUTTON4_PORT           PORTD                           // Serial Data Output Port
#define BUTTON4_DDR            DDRD                            // Serial Data Output DDR
#define BUTTON4_INPUT          PIND                            // Serial Data Output Input
#define BUTTON4_PIN            PD4                             // Serial Data Output Pin
#define BUTTON4_READ           (BUTTON4_INPUT & (1<<BUTTON4_PIN))    // Serial Data Output Read Pin
#define BUTTON4_SET_HIGH       BUTTON4_PORT |= (1<<BUTTON4_PIN)
#define BUTTON4_SET_LOW        BUTTON4_PORT &= ~(1<<BUTTON4_PIN)
#define BUTTON4_SET_INPUT      BUTTON4_DDR &= ~(1<<BUTTON4_PIN); BUTTON4_SET_HIGH
#define BUTTON4_SET_OUTPUT     BUTTON4_DDR |= (1<<BUTTON4_PIN);  BUTTON4_SET_LOW

#define CE_NRF_PORT           PORTB                           // Serial Data Output Port
#define CE_NRF_DDR            DDRB                            // Serial Data Output DDR
#define CE_NRF_INPUT          PINB                            // Serial Data Output Input
#define CE_NRF_PIN            PB3                             // Serial Data Output Pin
#define CE_NRF_READ           (CE_NRF_INPUT & (1<<CE_NRF_PIN))    // Serial Data Output Read Pin
#define CE_NRF_SET_HIGH       CE_NRF_PORT |= (1<<CE_NRF_PIN)
#define CE_NRF_SET_LOW        CE_NRF_PORT &= ~(1<<CE_NRF_PIN)
#define CE_NRF_SET_INPUT      CE_NRF_DDR &= ~(1<<CE_NRF_PIN); CE_NRF_SET_HIGH
#define CE_NRF_SET_OUTPUT     CE_NRF_DDR |= (1<<CE_NRF_PIN);  CE_NRF_SET_LOW
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
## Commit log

2017-06-08 Siddharth Talesra
